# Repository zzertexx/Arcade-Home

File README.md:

# Arcade@Home
Console with games, outputting HDMI and Joysticks to control it

## What is it?
It is a combo of joysticks and main console which offers pixel games to play in multiplayer on any display with HDMI

## Why did I build it?
I saw that a lot of people did tamagotchi during their way, so I wanted to do similar but ended at gaming console 
I took my little bro with me to teach him hardware

## How to recreate it?
1. Order both PCBs
2. 3D Print enclosures
3. Assemble hardware
4. Flush Firmware(not ready yet)
5. Connect HDMI
6. Play!

## Future Plans:
* Enclosure for Joystick
* Firmware for ESP32
* Firmware for 

## Bill of Materials
| Name | Price |
| --- | --- |
| XUNPU HDMI-001S | 0.25$ |
| RP2350A | 1.3$ |
| JST 3 pin | 0.1$ |
| onsemi NCP1117 3.3V DPO | 0.25$ |
| Flash Memory W25Q128JVSIQ | 2.6$ |
| Tactile Button x2 | 0.04$ |
| Type C x2 | 1.5$ |
| Pi Radio Module 2 | 5.00$ |
| +1v1 buck | 0,4$ |
| Green LED 0603 x2 | 0.02$ |
| Header Pins | 0.15$ |
| SS34 | 0,03$ |
| 4.7uF 0603 x3 | 0.1$ |
| 100nF 0603 x14 | 0.12$ |
| 10uF 0805 x3 | 0.12$ |
| 15pF 0402 x2 | 0.04$ |
| 3.3uH 0806 | 0.3$ |
| 2.2uH | 0.1$ |
| 27R 0603 x2 | 0.00$ |
| 33R 0603 | 0.00$ |
| 5.1KR 0603 x2 | 0.00$ | 
| 220R x5 | 0.01$ |
| 270R 0603 x9 | 0.02$ |
| 1K 0603 x6 | 0.01$ |
| 1.2K | 0.01$ |
| 4.7K x2 | 0.01$ |
| 10K 0603 x2 | 0.01$ |
| 100R 0603 x3 | 0.00$ |
| 470R 0603 x2 | 0.01$ |
| 120K 0603 | 0.00$ | 
| 100K 0603 | 0.00$ | 
| Push Button x4 | 4.24$ |
| ESP32 - SuperMini | 2.00$ |
| Turn-ON Button | 1.3$ |
| Microswitch x4 | 2$ |
| TP4056 | 0.09$ |
| FS8205A | 0.06$ |
| DW01A | 0.03$ |
| Total | 8.6$ |

## Images

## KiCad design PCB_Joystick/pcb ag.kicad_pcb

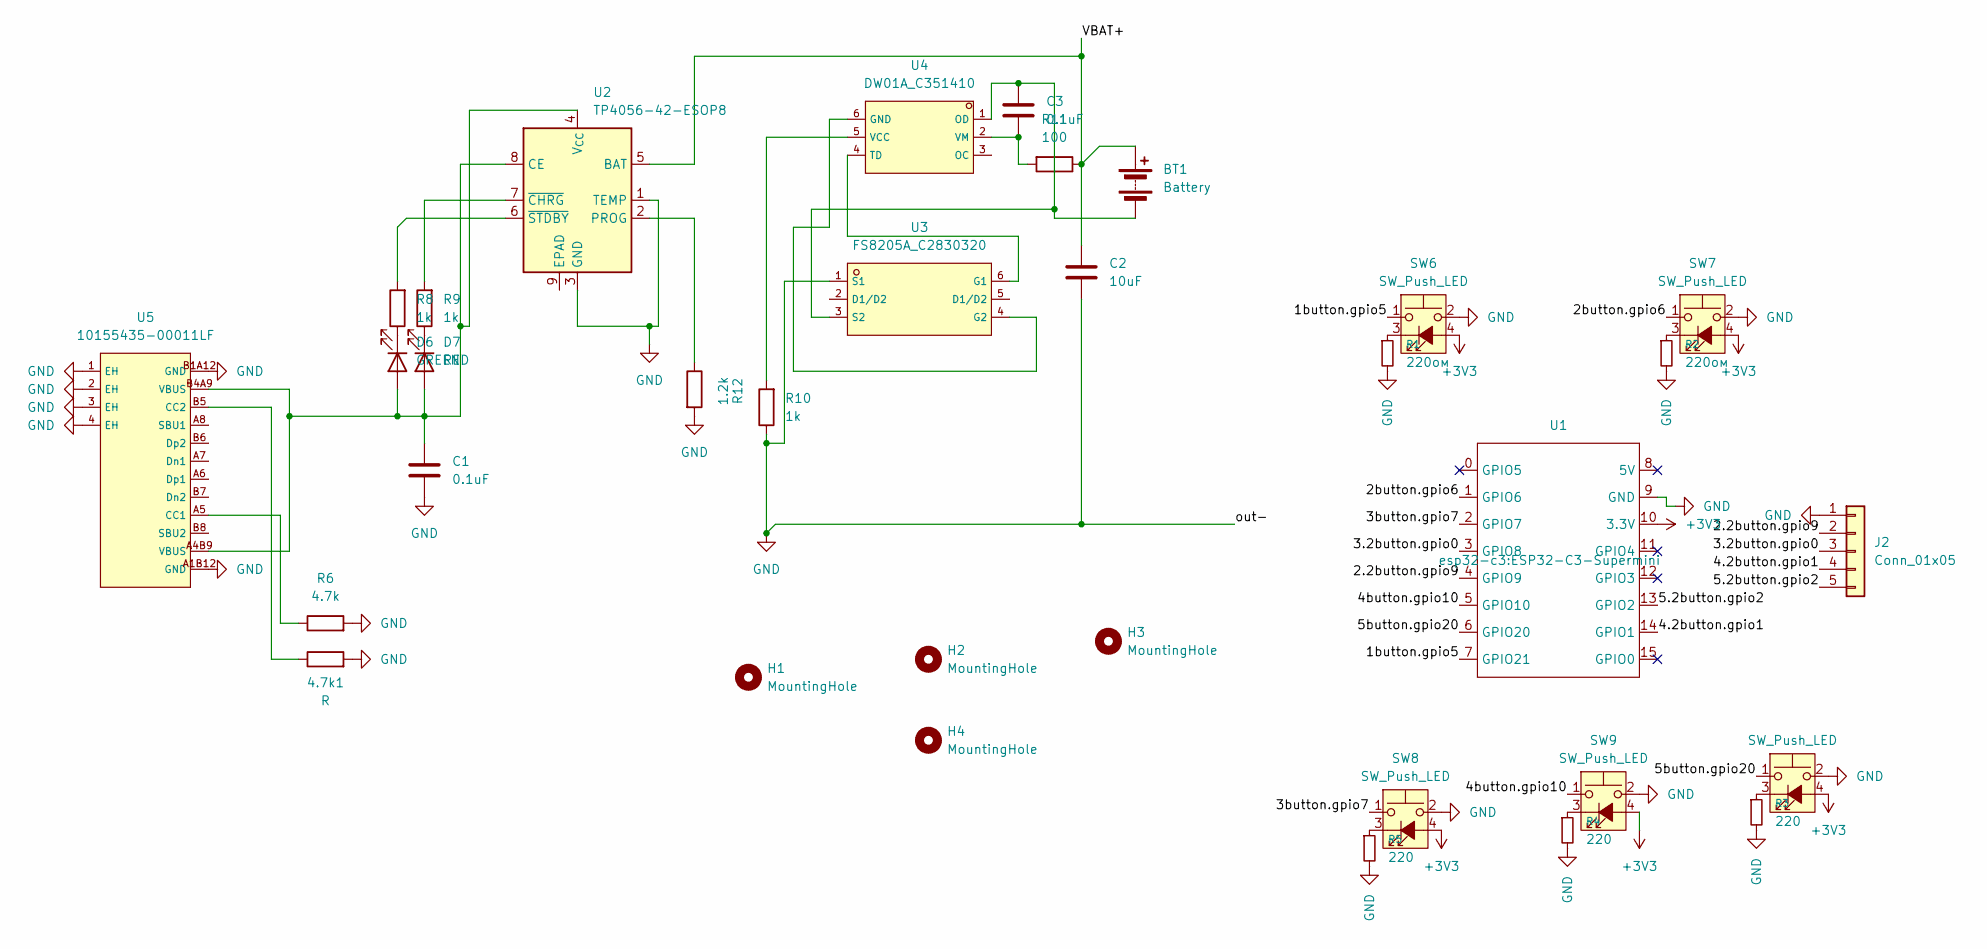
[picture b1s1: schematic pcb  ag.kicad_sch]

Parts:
4.7k1: R; R_0603_1608Metric_Pad0.98x0.95mm_HandSolder
BT1: Battery; PinHeader_1x02_P2.54mm_Vertical
C1, C3: 0.1uF; C_0603_1608Metric_Pad1.08x0.95mm_HandSolder
C2: 10uF; C_0603_1608Metric_Pad1.08x0.95mm_HandSolder
D6: GREEN; LED_0603_1608Metric_Pad1.05x0.95mm_HandSolder
D7: RED; LED_0603_1608Metric_Pad1.05x0.95mm_HandSolder
H1, H2, H3, H4: MountingHole; MountingHole_2.5mm
J2: Conn_01x05; PinHeader_1x05_P2.54mm_Vertical
R1, R2: 220ом; R_0603_1608Metric_Pad0.98x0.95mm_HandSolder
R3, R4, R5: 220; R_0603_1608Metric_Pad0.98x0.95mm_HandSolder
R6: 4.7k; R_0603_1608Metric_Pad0.98x0.95mm_HandSolder
R8, R9, R10: 1k; R_0603_1608Metric_Pad0.98x0.95mm_HandSolder
R11: 100; R_0603_1608Metric_Pad0.98x0.95mm_HandSolder
R12: 1.2k; R_0603_1608Metric_Pad0.98x0.95mm_HandSolder
SW6, SW7, SW8, SW9, SW10: SW_Push_LED; FanPinHeader_1x04_P2.54mm_Vertical
U1: ESP32-C3-Supermini
U2: TP4056-42-ESOP8; ESOP-8_L4.9-W3.9-P1.27-LS6.0-BL-EP
U3: FS8205A_C2830320; SOT-23-6_L2.9-W1.6-P0.95-LS2.8-BR; LCSC C2830320
U4: DW01A_C351410; SOT-23-6_L2.9-W1.6-P0.95-LS2.8-BL; LCSC C351410
U5: 10155435-00011LF; USB-C-SMD_10155435-00011LF; LCSC C5409177

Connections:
+3V3: SW6.4 (A), SW7.4 (A), SW8.4 (A), SW9.4 (A), SW10.4 (A), U1.10 (3.3V)
/1button.gpio5: SW6.1, U1.7 (GPIO21)
/2.2button.gpio9: J2.2, U1.4 (GPIO9)
/2button.gpio6: SW7.1, U1.1 (GPIO6)
/3.2button.gpio0: J2.3, U1.3 (GPIO8)
/3button.gpio7: SW8.1, U1.2 (GPIO7)
/4.2button.gpio1: J2.4, U1.14 (GPIO1)
/4button.gpio10: SW9.1, U1.5 (GPIO10)
/5.2button.gpio2: J2.5, U1.13 (GPIO2)
/5button.gpio20: SW10.1, U1.6 (GPIO20)
/VBAT+: BT1.1 (+), C2.1, R11.1, U2.5 (BAT)
GND: 4.7k1.2, C1.2, C2.2, J2.1, R1.2, R2.2, R3.2, R4.2, R5.2, R6.2, R10.1, R12.2, SW6.2, SW7.2, SW8.2, SW9.2, SW10.2, U1.9 (GND), U2.1 (TEMP), U2.3 (GND), U3.1 (S1), U5.1 (EH), U5.2 (EH), U5.3 (EH), U5.4 (EH), U5.A1B12 (GND), U5.B1A12 (GND)
unnamed: BT1.2 (-), C3.1, U3.3 (S2), U4.1 (OD)
unnamed: C1.1, D6.2 (A), D7.2 (A), U2.4 (V_{CC}), U2.8 (CE), U5.A4B9 (VBUS), U5.B4A9 (VBUS)
unnamed: D6.1 (K), R8.1
unnamed: D7.1 (K), R9.1
unnamed: R1.1, SW6.3 (K)
unnamed: R2.1, SW7.3 (K)
unnamed: R5.1, SW8.3 (K)
unnamed: R4.1, SW9.3 (K)
unnamed: R3.1, SW10.3 (K)
unnamed: R12.1, U2.2 (PROG)
unnamed: R9.2, U2.7 (~CHRG)
unnamed: R8.2, U2.6 (~STDBY)
unnamed: U3.6 (G1), U4.4 (TD)
unnamed: U3.4 (G2), U4.6 (GND)
unnamed: R10.2, U4.5 (VCC)
unnamed: C3.2, R11.2, U4.2 (VM)
unnamed: R6.1, U5.A5 (CC1)
unnamed: 4.7k1.1, U5.B5 (CC2)

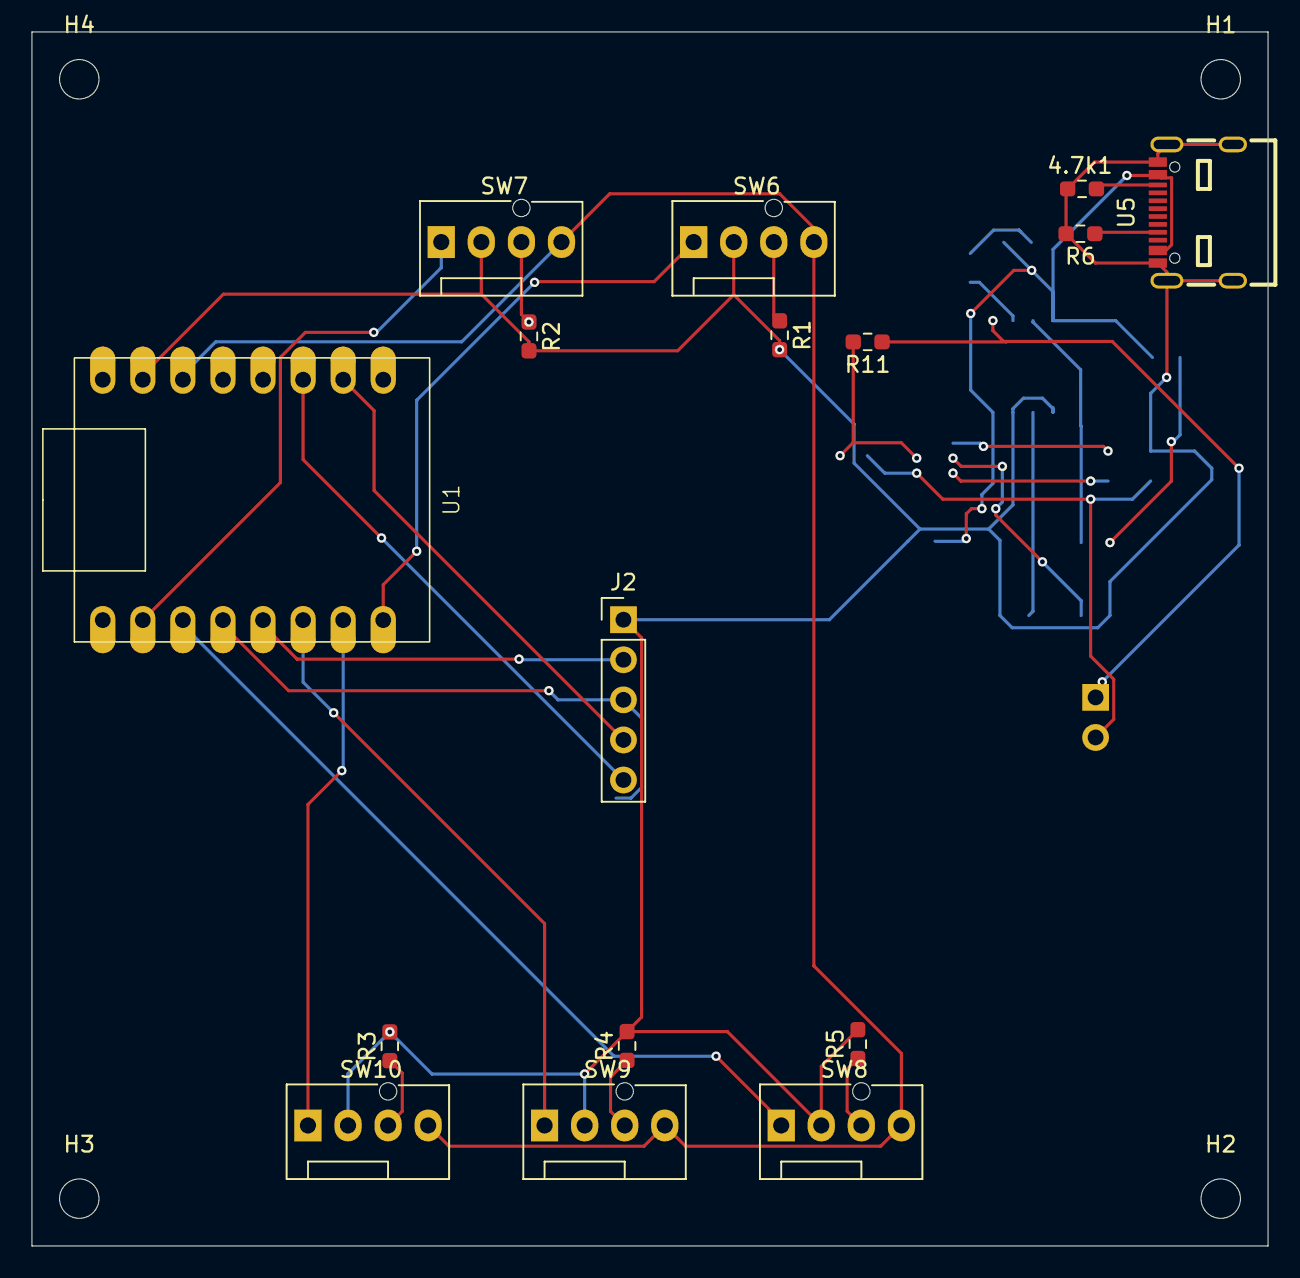
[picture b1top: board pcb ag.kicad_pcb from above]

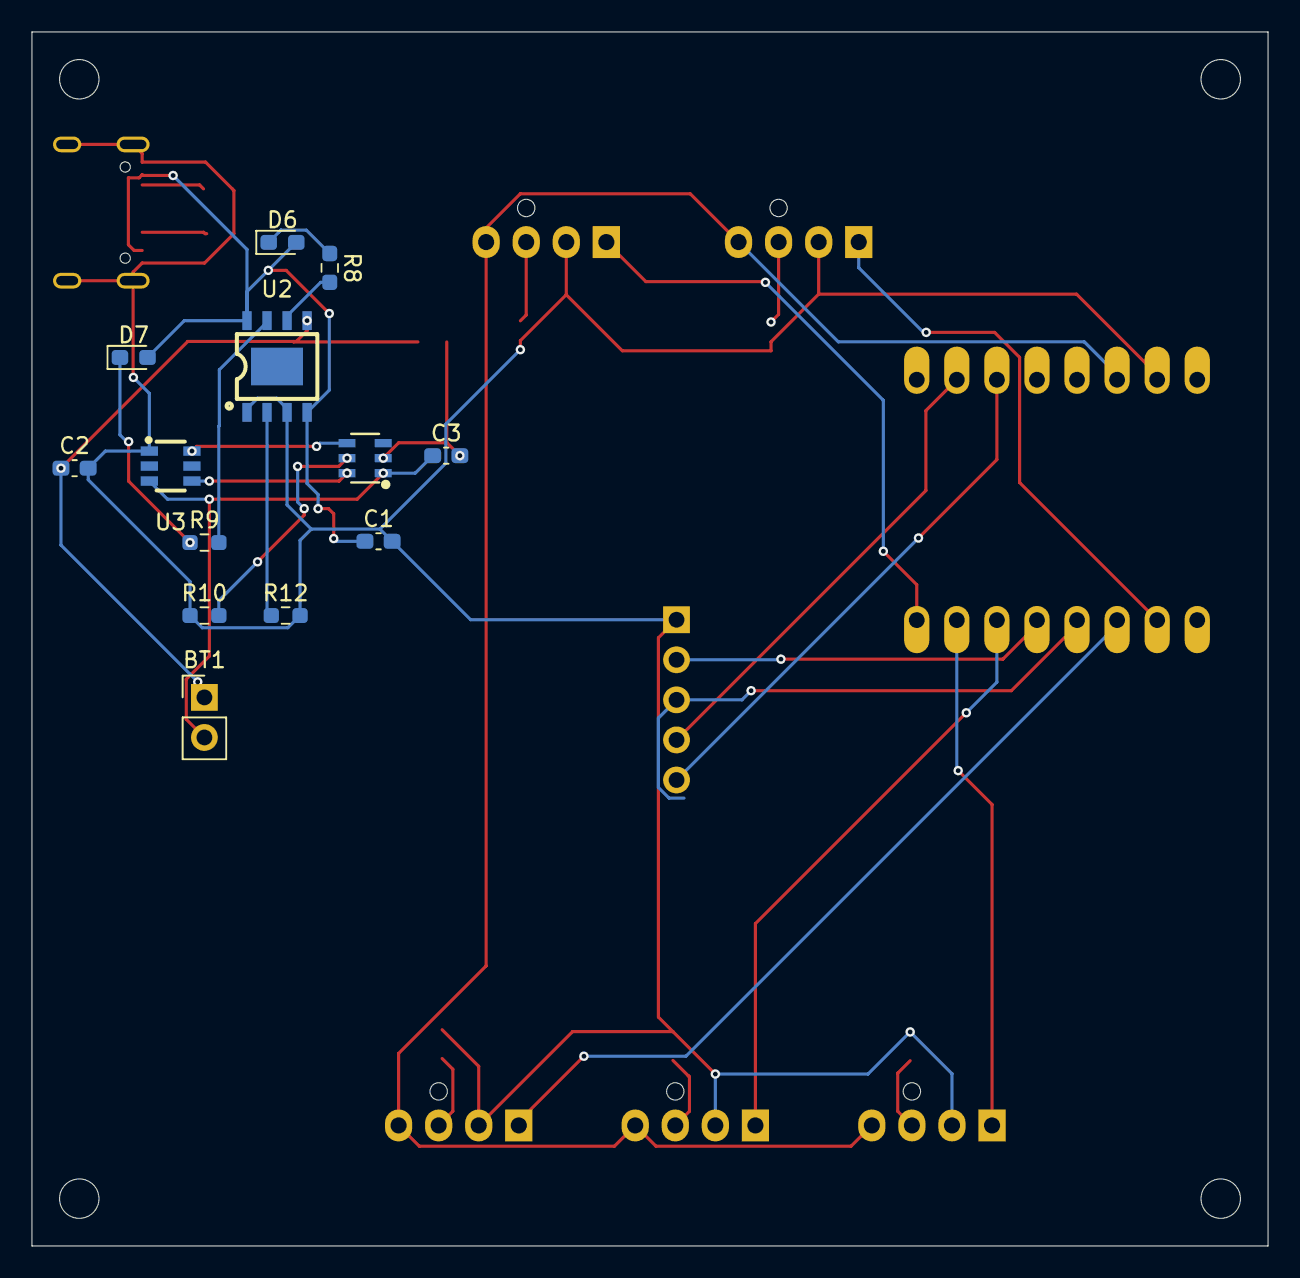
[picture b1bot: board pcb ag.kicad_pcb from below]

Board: 2 copper layers, 78.4 x 77.0 mm, 33 parts (13 on the bottom side), 30 nets.

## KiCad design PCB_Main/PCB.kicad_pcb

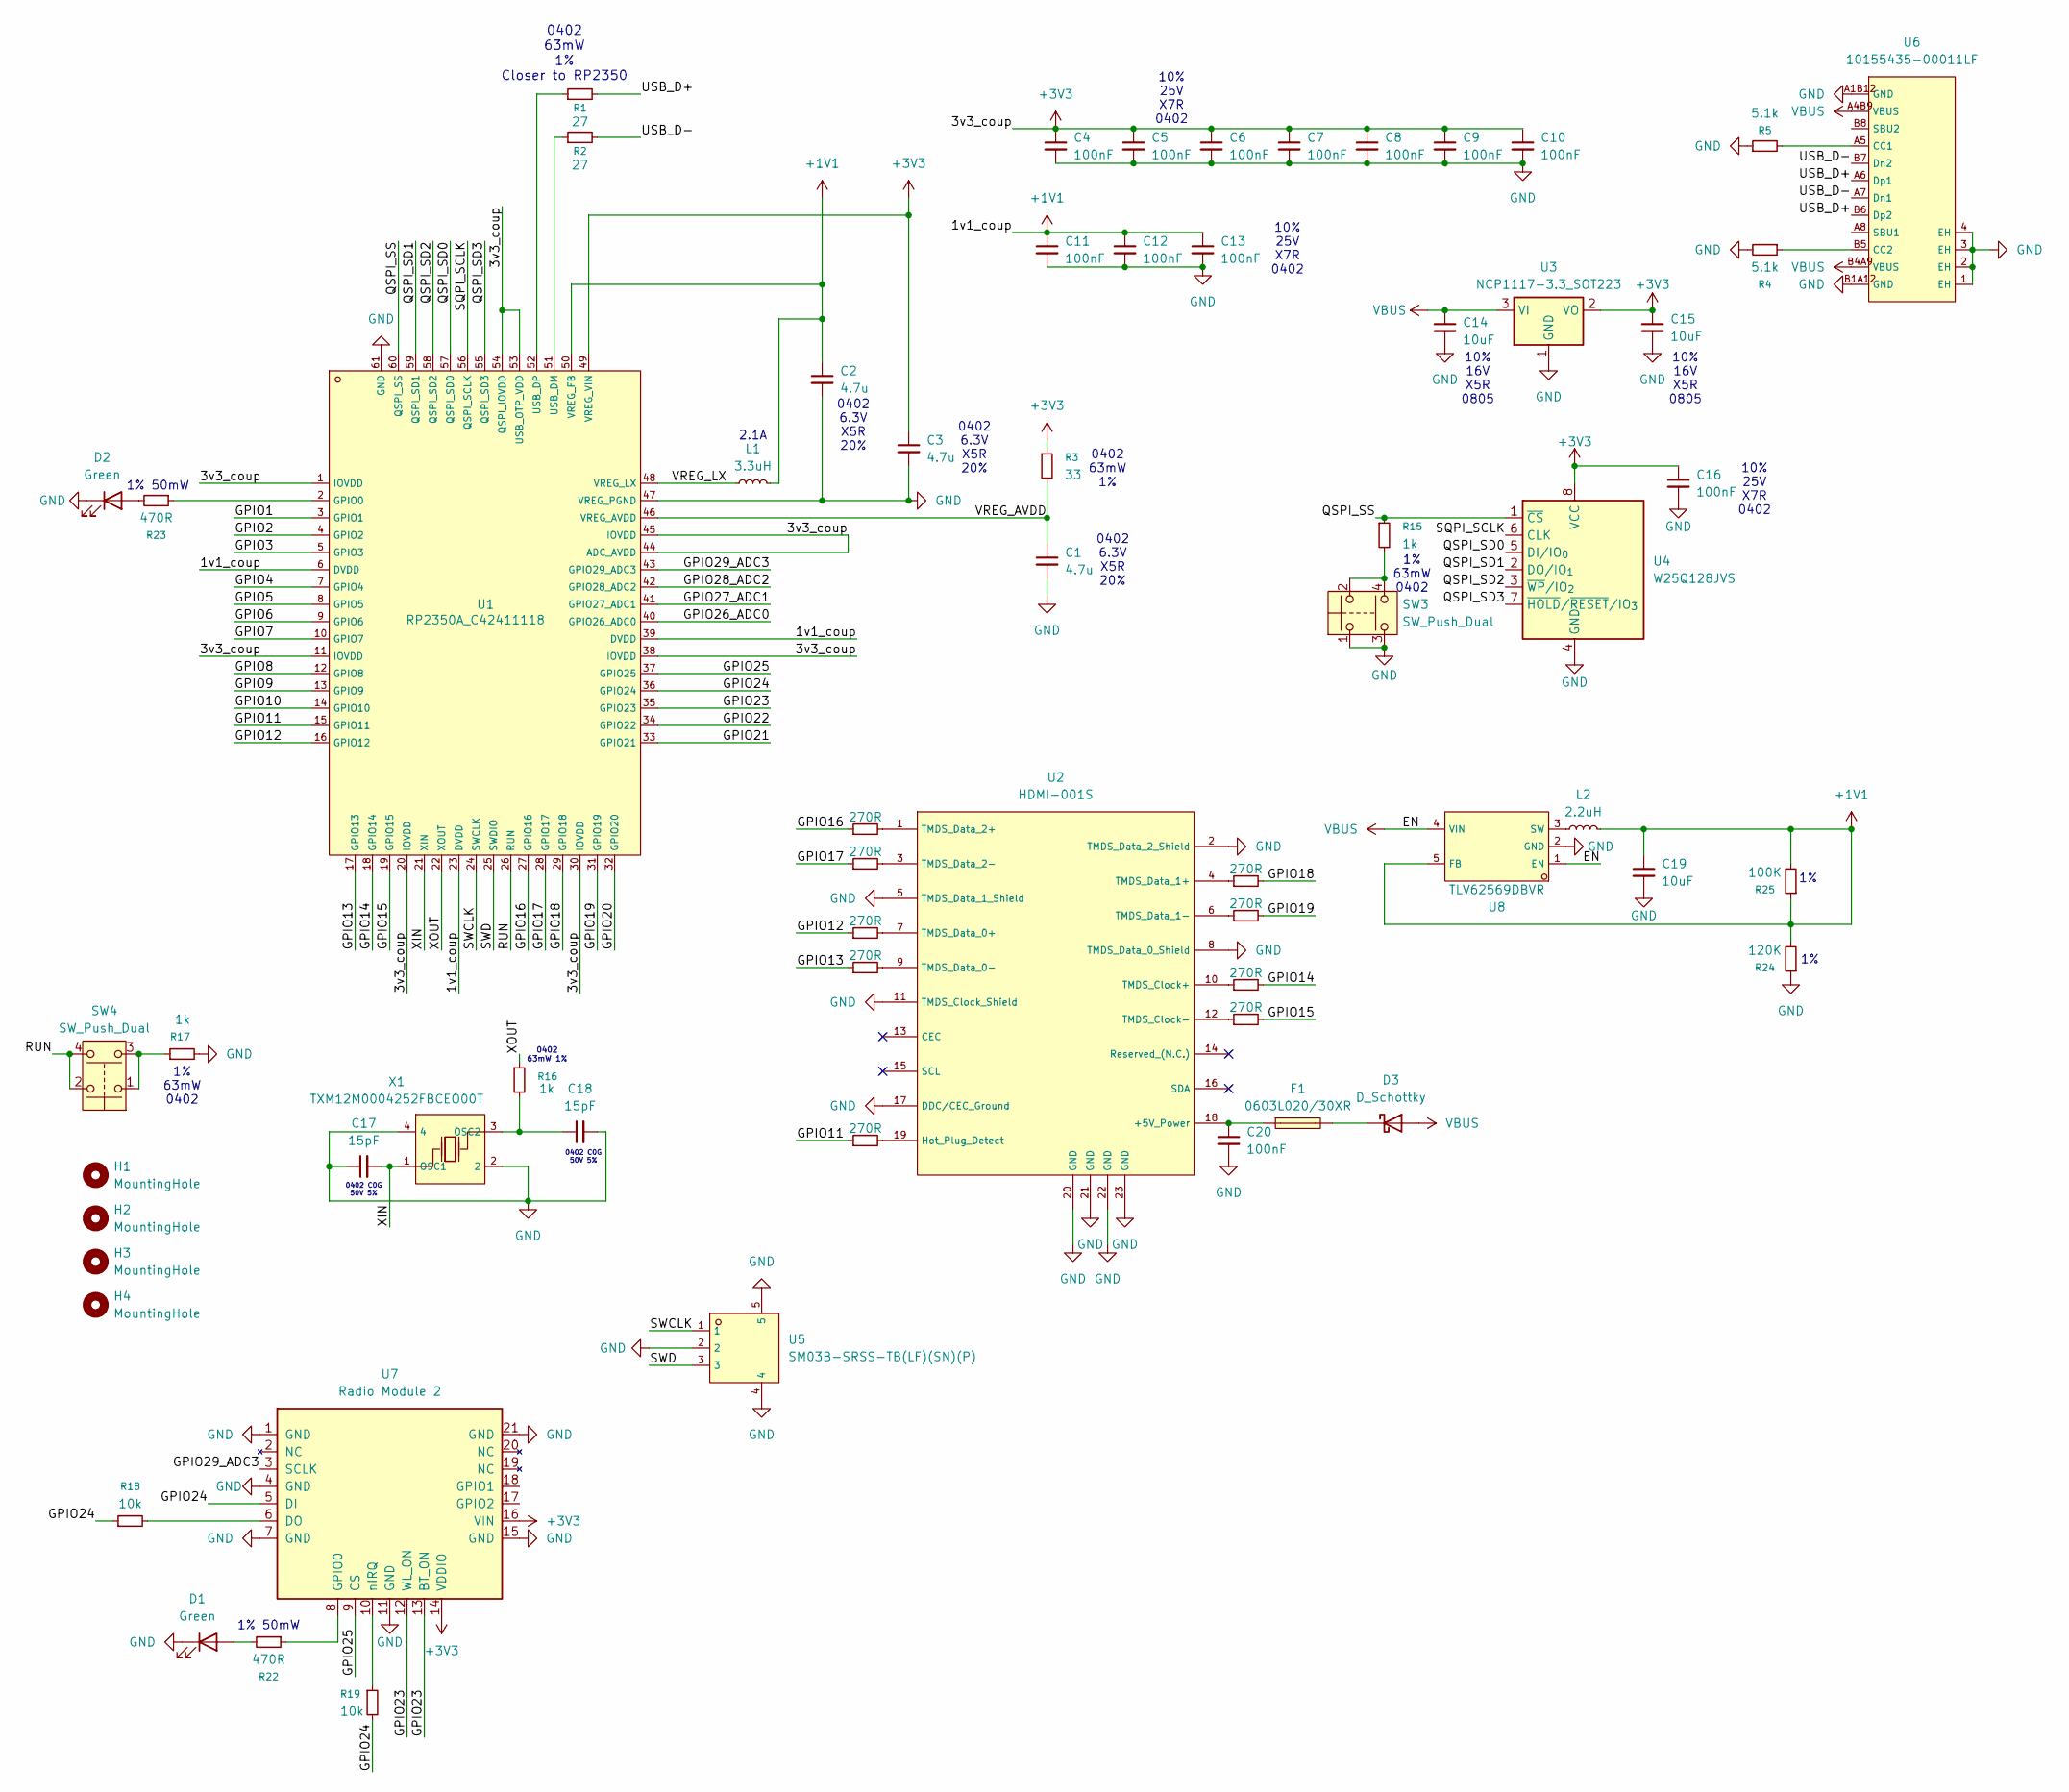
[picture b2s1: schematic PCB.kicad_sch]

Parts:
C1, C2, C3: 4.7u; C_0603_1608Metric_Pad1.08x0.95mm_HandSolder
C4, C5, C6, C7, C8, C9, C10, C11, C12, C13, C16, C20: 100nF; C_0603_1608Metric_Pad1.08x0.95mm_HandSolder
C14, C15, C19: 10uF; C_0805_2012Metric_Pad1.18x1.45mm_HandSolder
C17, C18: 15pF; C_0402_1005Metric_Pad0.74x0.62mm_HandSolder
D1, D2: Green; LED_0603_1608Metric_Pad1.05x0.95mm_HandSolder
D3: D_Schottky; D_SOD-123
F1: 0603L020/30XR; F0603; LCSC C20608677
H1, H2, H3, H4: MountingHole; MountingHole_2.5mm
L1: 3.3uH; IND-SMD_L2.0-W1.6_AOTA-B201610S3R3-101-T
L2: 2.2uH; L_APV_ANR6028
R1, R2: 27; R_0603_1608Metric_Pad0.98x0.95mm_HandSolder
R3: 33; R_0603_1608Metric_Pad0.98x0.95mm_HandSolder
R4, R5: 5.1k; R_0603_1608Metric_Pad0.98x0.95mm_HandSolder
R6, R7, R8, R9, R10, R11, R12, R13, R14: 270R; R_0603_1608Metric_Pad0.98x0.95mm_HandSolder
R15, R16, R17: 1k; R_0603_1608Metric_Pad0.98x0.95mm_HandSolder
R18, R19: 10k; R_0603_1608Metric_Pad0.98x0.95mm_HandSolder
R22, R23: 470R; R_0603_1608Metric_Pad0.98x0.95mm_HandSolder
R24: 120K; R_0603_1608Metric_Pad0.98x0.95mm_HandSolder
R25: 100K; R_0603_1608Metric_Pad0.98x0.95mm_HandSolder
SW3, SW4: SW_Push_Dual; SW-SMD_4P-L6.0-W6.0-P4.50-LS7.2
U1: RP2350A_C42411118; QFN-60_L7.0-W7.0-P0.40-TL-EP3.4; LCSC C42411118
U2: HDMI-001S; HDMI-SMD_HDMI-001S; LCSC C720616
U3: NCP1117-3.3_SOT223; SOT-223-3_TabPin2
U4: W25Q128JVS; SOIC-8_5.3x5.3mm_P1.27mm
U5: SM03B-SRSS-TB(LF)(SN)(P); CONN-SMD_SM03B-SRSS-TB-LF-SN-P; LCSC C160403
U6: 10155435-00011LF; USB-C-SMD_10155435-00011LF; LCSC C5409177
U7: Radio Module 2; rpi_rmc20452t
U8: TLV62569DBVR; SOT-23-5_L3.0-W1.7-P0.95-LS2.8-BR; LCSC C141836
X1: TXM12M0004252FBCEO00T; OSC-SMD_4P-L2.5-W2.0-BL; LCSC C284155

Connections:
+1V1: C2.1, C11.1, C12.1, C13.1, C19.1, L1.2, L2.2, R24.2, R25.1, R25.2, U1.6 (DVDD), U1.23 (DVDD), U1.39 (DVDD), U1.50 (VREG_FB), U8.5 (FB)
+3V3: C3.1, C4.1, C5.1, C6.1, C7.1, C8.1, C9.1, C10.1, C15.1, C16.1, R3.1, U1.1 (IOVDD), U1.11 (IOVDD), U1.20 (IOVDD), U1.30 (IOVDD), U1.38 (IOVDD), U1.44 (ADC_AVDD), U1.45 (IOVDD), U1.49 (VREG_VIN), U1.53 (USB_OTP_VDD), U1.54 (QSPI_IOVDD), U3.2 (VO), U4.8 (VCC), U7.14 (VDDIO), U7.16 (VIN)
/GPIO1: U1.3 (GPIO1)
/GPIO2: U1.4 (GPIO2)
/GPIO3: U1.5 (GPIO3)
/GPIO4: U1.7 (GPIO4)
/GPIO5: U1.8 (GPIO5)
/GPIO6: U1.9 (GPIO6)
/GPIO7: U1.10 (GPIO7)
/GPIO8: U1.12 (GPIO8)
/GPIO9: U1.13 (GPIO9)
/GPIO10: U1.14 (GPIO10)
/GPIO11: R14.1, U1.15 (GPIO11)
/GPIO12: R10.1, U1.16 (GPIO12)
/GPIO13: R11.1, U1.17 (GPIO13)
/GPIO14: R12.2, U1.18 (GPIO14)
/GPIO15: R13.2, U1.19 (GPIO15)
/GPIO16: R6.1, U1.27 (GPIO16)
/GPIO17: R7.1, U1.28 (GPIO17)
/GPIO18: R8.2, U1.29 (GPIO18)
/GPIO19: R9.2, U1.31 (GPIO19)
/GPIO20: U1.32 (GPIO20)
/GPIO21: U1.33 (GPIO21)
/GPIO22: U1.34 (GPIO22)
/GPIO23: U1.35 (GPIO23), U7.12 (WL_ON), U7.13 (BT_ON)
/GPIO24: R18.1, R19.2, U1.36 (GPIO24), U7.5 (DI)
/GPIO25: U1.37 (GPIO25), U7.9 (CS)
/GPIO26_ADC0: U1.40 (GPIO26_ADC0)
/GPIO27_ADC1: U1.41 (GPIO27_ADC1)
/GPIO28_ADC2: U1.42 (GPIO28_ADC2)
/GPIO29_ADC3: U1.43 (GPIO29_ADC3), U7.3 (SCLK)
/QSPI_SD0: U1.57 (QSPI_SD0), U4.5 (DI/IO_{0})
/QSPI_SD1: U1.59 (QSPI_SD1), U4.2 (DO/IO_{1})
/QSPI_SD2: U1.58 (QSPI_SD2), U4.3 (~WP/IO_{2})
/QSPI_SD3: U1.55 (QSPI_SD3), U4.7 (~HOLD/~RESET/IO_{3})
/QSPI_SS: R15.1, U1.60 (QSPI_SS), U4.1 (~CS)
/RUN: SW4.2, SW4.4, U1.26 (RUN)
/SQPI_SCLK: U1.56 (QSPI_SCLK), U4.6 (CLK)
/SWCLK: U1.24 (SWCLK), U5.1
/SWD: U1.25 (SWDIO), U5.3
/USB_D+: R1.2, U6.A6 (Dp1), U6.B6 (Dp2)
/USB_D-: R2.2, U6.A7 (Dn1), U6.B7 (Dn2)
/VREG_AVDD: C1.1, R3.2, U1.46 (VREG_AVDD)
/VREG_LX: L1.1, U1.48 (VREG_LX)
/XIN: C17.2, U1.21 (XIN), X1.1 (OSC1)
/XOUT: R16.1, U1.22 (XOUT)
GND: C1.2, C2.2, C3.2, C4.2, C5.2, C6.2, C7.2, C8.2, C9.2, C10.2, C11.2, C12.2, C13.2, C14.2, C15.2, C16.2, C17.1, C18.2, C19.2, C20.2, D1.1 (K), D2.1 (K), R4.2, R5.1, R17.2, R24.1, SW3.1, SW3.3, U1.47 (VREG_PGND), U1.61 (GND), U2.2 (TMDS_Data_2_Shield), U2.5 (TMDS_Data_1_Shield), U2.8 (TMDS_Data_0_Shield), U2.11 (TMDS_Clock_Shield), U2.17 (DDC/CEC_Ground), U2.20 (GND), U2.21 (GND), U2.22 (GND), U2.23 (GND), U3.1 (GND), U4.4 (GND), U5.2, U5.4, U5.5, U6.1 (EH), U6.2 (EH), U6.3 (EH), U6.4 (EH), U6.A1B12 (GND), U6.B1A12 (GND), U7.1 (GND), U7.4 (GND), U7.7 (GND), U7.11 (GND), U7.15 (GND), U7.21 (GND), U8.2 (GND), X1.2, X1.4
unnamed: D1.2 (A), R22.2
unnamed: D2.2 (A), R23.2
unnamed: D3.1 (K), F1.2
unnamed: R15.2, SW3.2, SW3.4
unnamed: R17.1, SW4.1, SW4.3
unnamed: R23.1, U1.2 (GPIO0)
unnamed: R2.1, U1.51 (USB_DM)
unnamed: R1.1, U1.52 (USB_DP)
unnamed: C20.1, F1.1, U2.18 (+5V_Power)
unnamed: R14.2, U2.19 (Hot_Plug_Detect)
unnamed: R12.1, U2.10 (TMDS_Clock+)
unnamed: R13.1, U2.12 (TMDS_Clock-)
unnamed: R10.2, U2.7 (TMDS_Data_0+)
unnamed: R11.2, U2.9 (TMDS_Data_0-)
unnamed: R8.1, U2.4 (TMDS_Data_1+)
unnamed: R9.1, U2.6 (TMDS_Data_1-)
unnamed: R6.2, U2.1 (TMDS_Data_2+)
unnamed: R7.2, U2.3 (TMDS_Data_2-)
unnamed: R5.2, U6.A5 (CC1)
unnamed: R4.1, U6.B5 (CC2)
unnamed: R18.2, U7.6 (DO)
unnamed: R22.1, U7.8 (GPIO0)
unnamed: R19.1, U7.10 (nIRQ)
unnamed: L2.1, U8.3 (SW)
unnamed: C18.1, R16.2, X1.3 (OSC2)
VBUS: C14.1, D3.2 (A), U3.3 (VI), U6.A4B9 (VBUS), U6.B4A9 (VBUS), U8.1 (EN), U8.4 (VIN)

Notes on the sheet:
0402 63mW 1% Closer to RP2350
1% 50mW
0402 6.3V X5R 20%
10% 16V X5R 0805
0402 63mW 1%
10% 25V X7R 0402
0402 63mW 1%
1% 63mW 0402
0402 C0G 50V 5%
2.1A

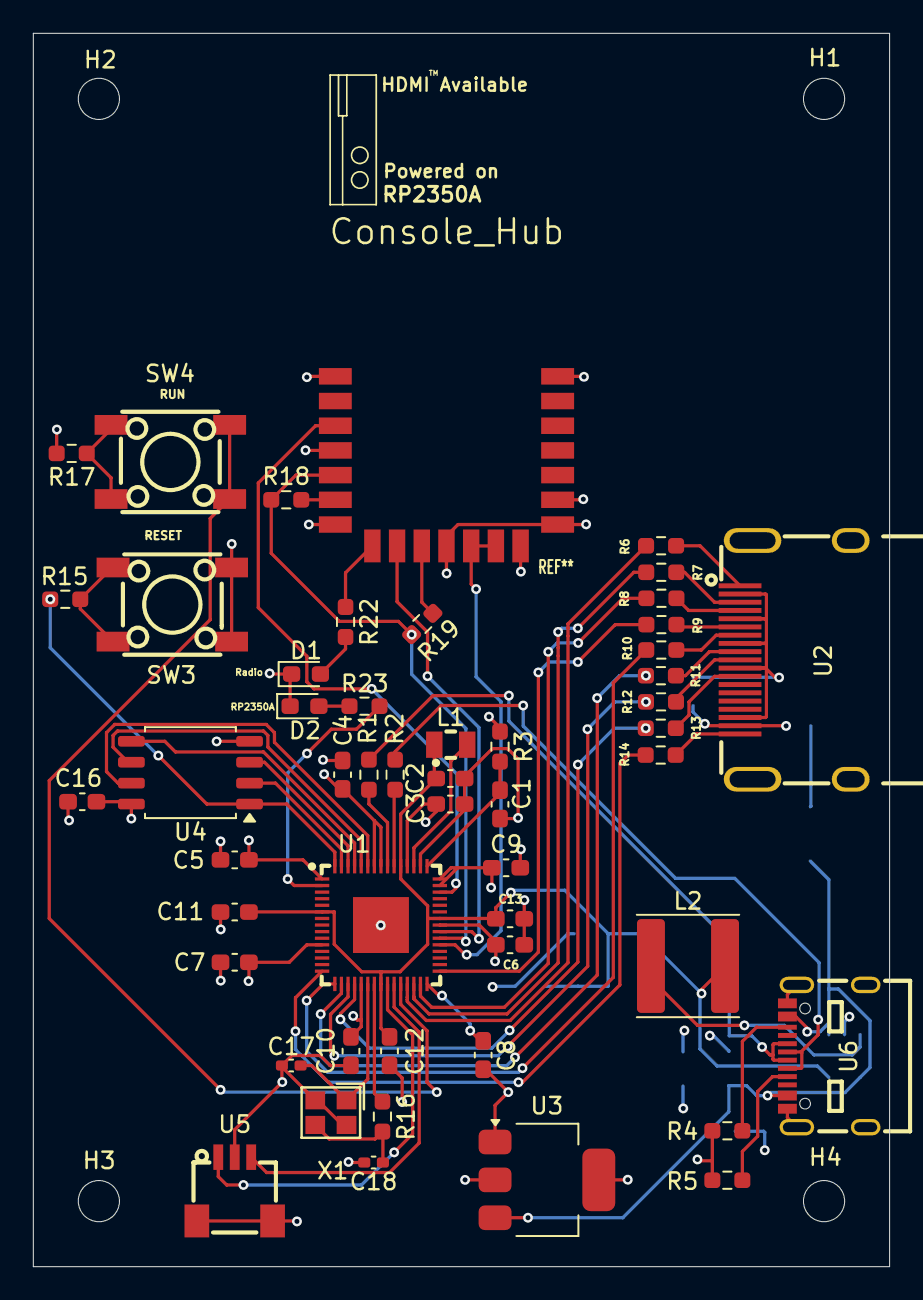
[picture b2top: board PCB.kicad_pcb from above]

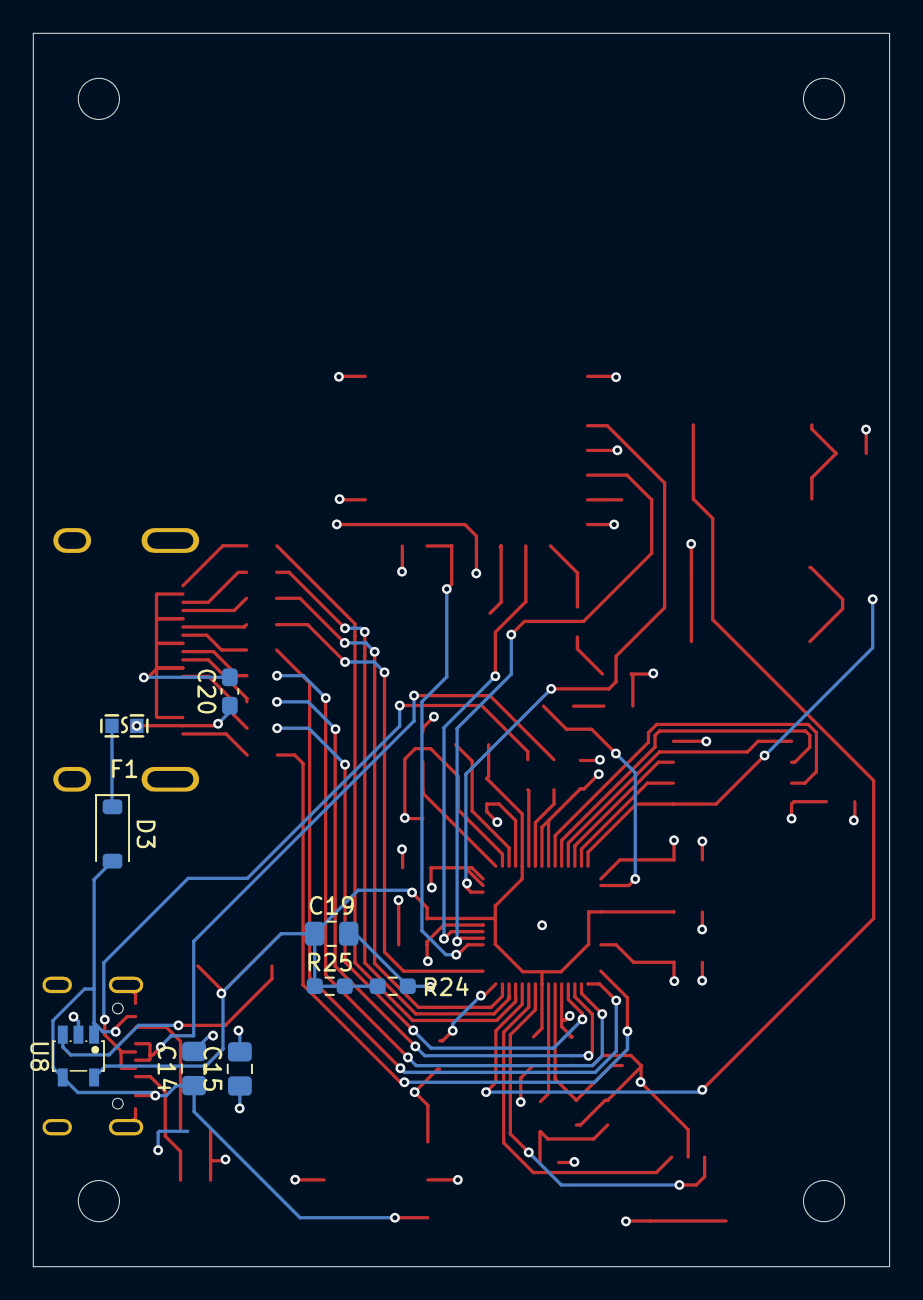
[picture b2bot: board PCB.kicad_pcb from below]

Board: 4 copper layers, 52.0 x 74.9 mm, 64 parts (9 on the bottom side), 57 nets.
